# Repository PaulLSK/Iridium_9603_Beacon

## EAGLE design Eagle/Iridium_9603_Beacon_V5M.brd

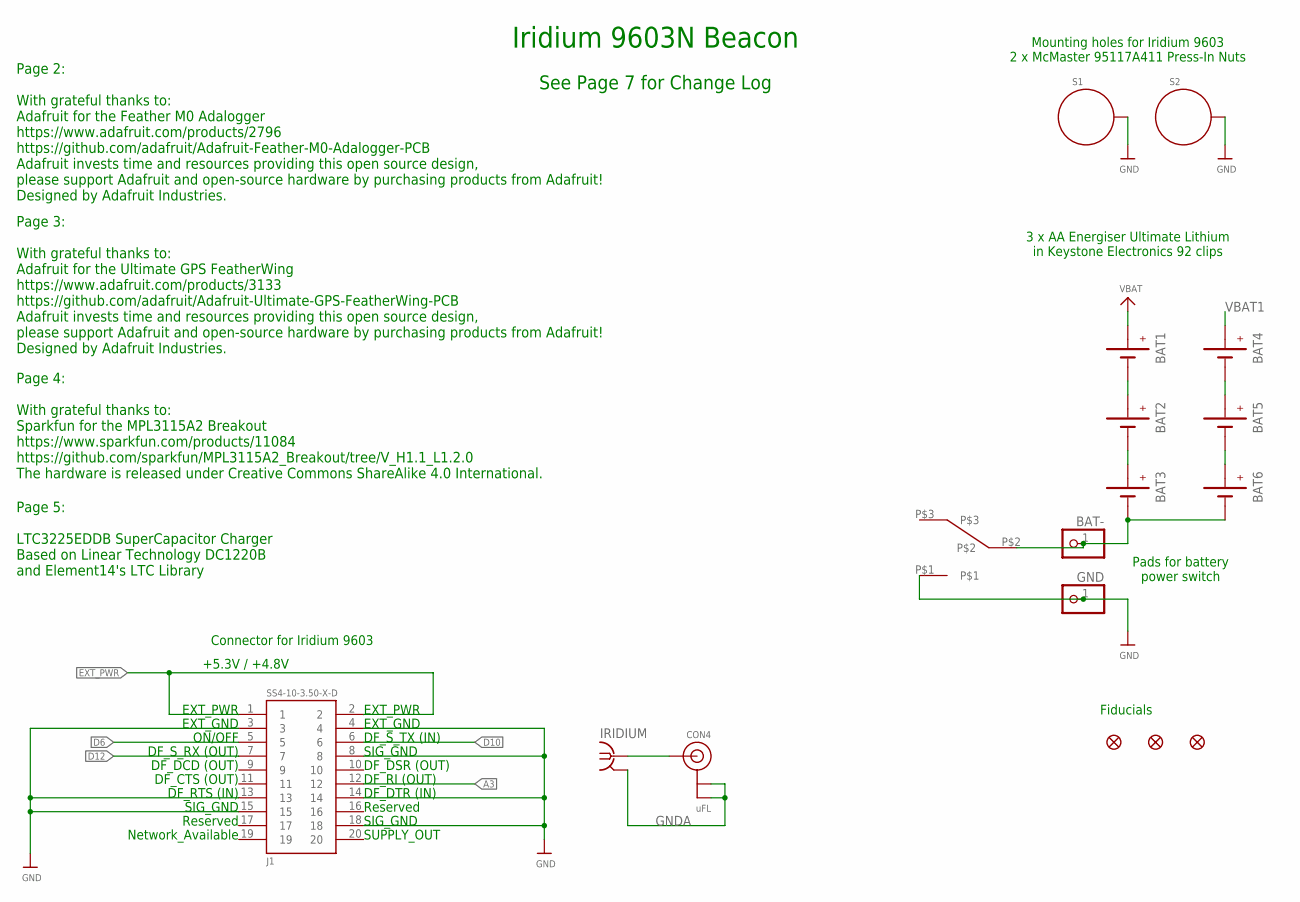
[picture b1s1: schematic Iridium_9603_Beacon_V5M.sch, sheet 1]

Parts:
BAT1, BAT2, BAT3, BAT4, BAT5, BAT6: BATTERYKEYSTONE92; BATTERY-AAA-KEYSTONE92
BAT-: PINHD-1X1; 1X01
CON4: uFL; U.FL
FD1, FD2, FD3: FIDUCIAL1X2; FIDUCIAL-1X2
GND: PINHD-1X1; 1X01
IRIDIUM: SMA-142-0711-821/826; J502-ND-142-0711-821/826
J1: SS4-10-3.50-X-D
S1, S2: STANDOFF_ELECTRICALMCMASTER-95117A411; STANDOFF-ELECTRICAL-MCMASTER-95117A411
U53: 7101K2AV2QE; AV2_SPDT

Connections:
A3: J1.12; also elsewhere on the board
D6: J1.5; also elsewhere on the board
D10: J1.6; also elsewhere on the board
D12: J1.7; also elsewhere on the board
EXT_PWR: J1.1, J1.2; also elsewhere on the board
GND: GND.1, J1.3, J1.4, J1.8, J1.13, J1.14, J1.15, J1.18, S1.P1, S2.P1, U53.P$1; also elsewhere on the board
GNDA: CON4.1 (GND), CON4.2 (GND), IRIDIUM.G@1 (2), IRIDIUM.G@2 (2), IRIDIUM.G@3 (2), IRIDIUM.G@4 (2)
unnamed: CON4.3 (SIGNAL), IRIDIUM.1
unnamed: BAT1.GND@1 (-), BAT1.GND@2 (-), BAT2.PWR@1 (+), BAT2.PWR@2 (+)
unnamed: BAT3.GND@1 (-), BAT3.GND@2 (-), BAT6.GND@1 (-), BAT6.GND@2 (-), BAT-.1, U53.P$2
unnamed: BAT2.GND@1 (-), BAT2.GND@2 (-), BAT3.PWR@1 (+), BAT3.PWR@2 (+)
unnamed: BAT4.GND@1 (-), BAT4.GND@2 (-), BAT5.PWR@1 (+), BAT5.PWR@2 (+)
unnamed: BAT5.GND@1 (-), BAT5.GND@2 (-), BAT6.PWR@1 (+), BAT6.PWR@2 (+)
VBAT: BAT1.PWR@1 (+), BAT1.PWR@2 (+); also elsewhere on the board
VBAT1: BAT4.PWR@1 (+), BAT4.PWR@2 (+); also elsewhere on the board

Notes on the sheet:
3 x AA Energiser Ultimate Lithium in Keystone Electronics 92 clips
Connector for Iridium 9603
Mounting holes for Iridium 9603 2 x McMaster 95117A411 Press-In Nuts
Iridium 9603N Beacon
Page 2: With grateful thanks to: Adafruit for the Feather M0 Adalogger https://www.adafruit.com/products/2796 https://github.com/adafruit/Adafruit-Feather-M0-Adalogger-PCB Adafruit invests time and resources providing this open source design, please support Adafruit and open-source hardware by purc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
Page 3: With grateful thanks to: Adafruit for the Ultimate GPS FeatherWing https://www.adafruit.com/products/3133 https://github.com/adafruit/Adafruit-Ultimate-GPS-FeatherWing-PCB Adafruit invests time and resources providing this open source design, please support Adafruit and open-source hardware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
Page 4: With grateful thanks to: Sparkfun for the MPL3115A2 Breakout https://www.sparkfun.com/products/11084 https://github.com/sparkfun/MPL3115A2_Breakout/tree/V_H1.1_L1.2.0 The hardware is released under Creative Commons ShareAlike 4.0 International.
EXT_PWR
EXT_GND
ON/OFF
DF_S_RX (OUT)
DF_DCD (OUT)
DF_CTS (OUT)
DF_RTS (IN)
SIG_GND
Reserved
Network_Available
DF_S_TX (IN)
DF_DSR (OUT)
DF_RI (OUT)
DF_DTR (IN)
SUPPLY_OUT
Page 5: LTC3225EDDB SuperCapacitor Charger Based on Linear Technology DC1220B and Element14's LTC Library
+5.3V / +4.8V
Fiducials
See Page 7 for Change Log
Pads for battery power switch

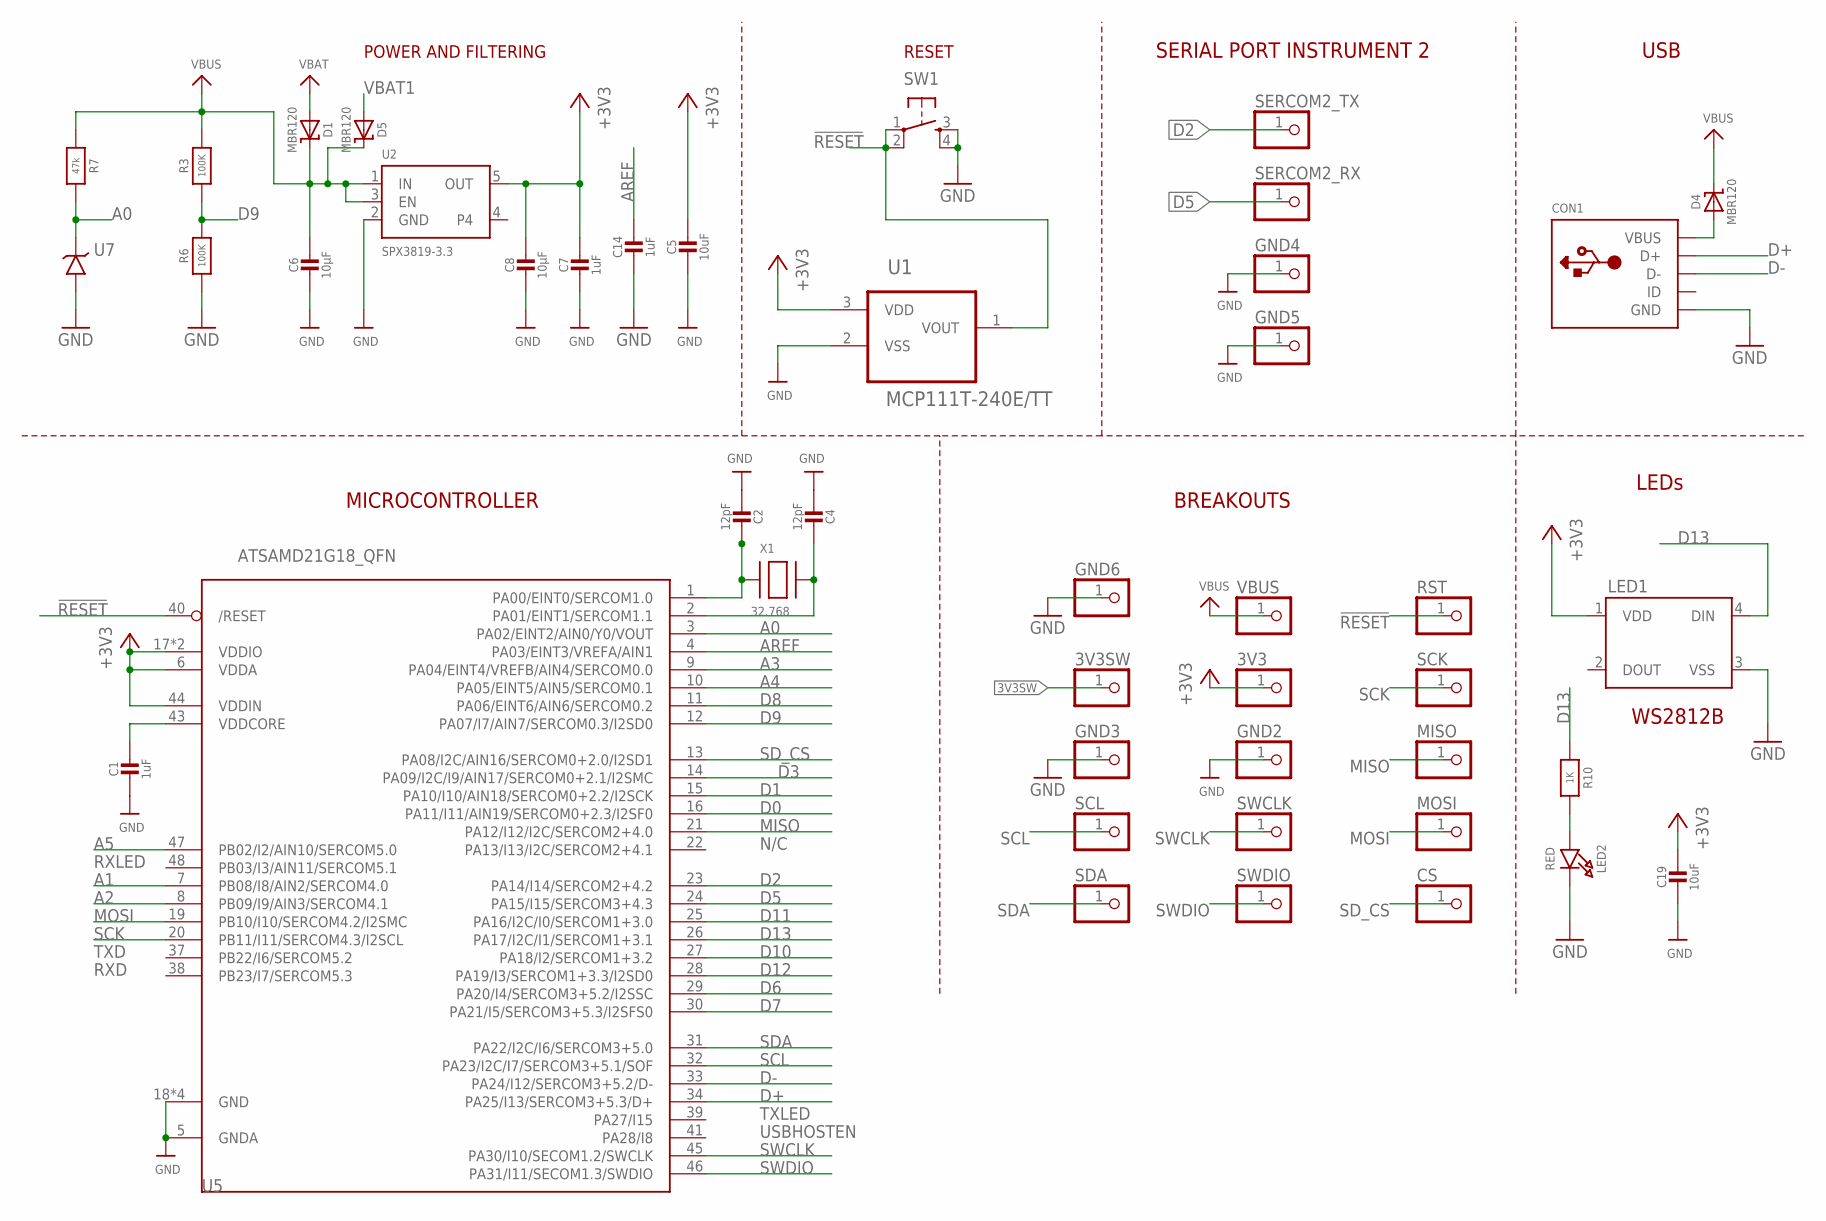
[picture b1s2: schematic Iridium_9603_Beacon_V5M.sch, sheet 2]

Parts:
3V3, 3V3SW: PINHD-1X1; 1X01
C1, C7, C14: 1uF; 0603-NO
C2, C4: 12pF; 0603-NO
C5, C19: 10uF; 0805-NO
C6, C8: 10µF; 0805-NO
CON1: USBFCI_10103594; FCI_10103594
CS: PINHD-1X1; 1X01
D1, D4, D5: MBR120; SOD-123
GND2, GND3, GND4, GND5, GND6: PINHD-1X1; 1X01
LED1: WS2812B
LED2: RED; CHIPLED_0805_NOOUTLINE
MISO: PINHD-1X1; 1X01
MOSI: PINHD-1X1; 1X01
R3, R6: 100K; 0805-NO
R7: 47k; 0603-NO
R10: 1K; 0603-NO
RST: PINHD-1X1; 1X01
SCK: PINHD-1X1; 1X01
SCL: PINHD-1X1; 1X01
SDA: PINHD-1X1; 1X01
SERCOM2_RX, SERCOM2_TX: PINHD-1X1; 1X01
SW1: SWITCH_SPST_4_PINRECT; TACTILE_SWITCH_SMD_4.6X2.8MM
SWCLK: PINHD-1X1; 1X01
SWDIO: PINHD-1X1; 1X01
U1: MCP111T-240E/TT; SOT95P237X112-3N; MPN MCP111T-240E/TT
U2: SPX3819-3.3; SOT23-5
U5: ATSAMD21G18_QFN; TQFN48_7MM
U7: LT1634-1,25BMCMS8; MSOP8
VBUS: PINHD-1X1; 1X01
X1: 32.768; XTAL3215

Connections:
3V3SW: 3V3SW.1; also elsewhere on the board
!RESET: RST.1, SW1.1, SW1.2, U1.1 (VOUT), U5.40 (/RESET)
+3V3: 3V3.1, C5.1, C7.1, C8.1, C19.1, LED1.1 (VDD), U1.3 (VDD), U2.5 (OUT), U5.6 (VDDA), U5.17 (VDDIO), U5.36 (VDDIO), U5.44 (VDDIN); also elsewhere on the board
A0: R7.2, U5.3 (PA02/EINT2/AIN0/Y0/VOUT), U7.6 (VOUT)
A1: U5.7 (PB08/I8/AIN2/SERCOM4.0); also elsewhere on the board
A2: U5.8 (PB09/I9/AIN3/SERCOM4.1)
A3: U5.9 (PA04/EINT4/VREFB/AIN4/SERCOM0.0); also elsewhere on the board
A4: U5.10 (PA05/EINT5/AIN5/SERCOM0.1)
A5: U5.47 (PB02/I2/AIN10/SERCOM5.0); also elsewhere on the board
AREF: C14.1, U5.4 (PA03/EINT3/VREFA/AIN1)
D0: U5.16 (PA11/I11/AIN19/SERCOM0+2.3/I2SF0); also elsewhere on the board
D1: U5.15 (PA10/I10/AIN18/SERCOM0+2.2/I2SCK); also elsewhere on the board
D2: SERCOM2_TX.1, U5.23 (PA14/I14/SERCOM2+4.2)
D3: U5.14 (PA09/I2C/I9/AIN17/SERCOM0+2.1/I2SMC); also elsewhere on the board
D5: SERCOM2_RX.1, U5.24 (PA15/I15/SERCOM3+4.3)
D6: U5.29 (PA20/I4/SERCOM3+5.2/I2SSC); also elsewhere on the board
D7: U5.30 (PA21/I5/SERCOM3+5.3/I2SFS0); also elsewhere on the board
D8: U5.11 (PA06/EINT6/AIN6/SERCOM0.2); also elsewhere on the board
D9: R3.1, R6.2, U5.12 (PA07/I7/AIN7/SERCOM0.3/I2SD0)
D10: U5.27 (PA18/I2/SERCOM1+3.2); also elsewhere on the board
D11: U5.25 (PA16/I2C/I0/SERCOM1+3.0); also elsewhere on the board
D12: U5.28 (PA19/I3/SERCOM1+3.3/I2SD0); also elsewhere on the board
D13: LED1.4 (DIN), R10.1, U5.26 (PA17/I2C/I1/SERCOM1+3.1)
D+: CON1.D+, U5.34 (PA25/I13/SERCOM3+5.3/D+)
D-: CON1.D-, U5.33 (PA24/I12/SERCOM3+5.2/D-)
GND: C1.2, C2.2, C4.2, C5.2, C6.2, C7.2, C8.2, C14.2, C19.2, CON1.BASE@1 (GND), CON1.BASE@2 (GND), CON1.GND, CON1.SPRT@1 (GND), CON1.SPRT@2 (GND), CON1.SPRT@3 (GND), CON1.SPRT@4 (GND), GND2.1, GND3.1, GND4.1, GND5.1, GND6.1, LED1.3 (VSS), LED2.C, R6.1, SW1.3, SW1.4, U1.2 (VSS), U2.2 (GND), U5.5 (GNDA), U5.18 (GND), U5.35 (GND), U5.42 (GND), U5.THERMAL (GND), U7.4 (GND); also elsewhere on the board
MISO: MISO.1, U5.21 (PA12/I12/I2C/SERCOM2+4.0)
MOSI: MOSI.1, U5.19 (PB10/I10/SERCOM4.2/I2SMC)
unnamed: LED2.A, R10.2
unnamed: C2.1, U5.1 (PA00/EINT0/SERCOM1.0), X1.P$1
unnamed: C4.1, U5.2 (PA01/EINT1/SERCOM1.1), X1.P$2
unnamed: CON1.VBUS, D4.A
SCK: SCK.1, U5.20 (PB11/I11/SERCOM4.3/I2SCL)
SCL: SCL.1, U5.32 (PA23/I2C/I7/SERCOM3+5.1/SOF); also elsewhere on the board
SDA: SDA.1, U5.31 (PA22/I2C/I6/SERCOM3+5.0); also elsewhere on the board
SD_CS: CS.1, U5.13 (PA08/I2C/AIN16/SERCOM0+2.0/I2SD1)
SWCLK: SWCLK.1, U5.45 (PA30/I10/SECOM1.2/SWCLK)
SWDIO: SWDIO.1, U5.46 (PA31/I11/SECOM1.3/SWDIO)
VBAT: D1.A; also elsewhere on the board
VBAT1: D5.A; also elsewhere on the board
VBUS: C6.1, D1.C, D4.C, D5.C, R3.2, R7.1, U2.1 (IN), U2.3 (EN), VBUS.1; also elsewhere on the board
VDDCORE1: C1.1, U5.43 (VDDCORE)

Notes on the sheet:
POWER AND FILTERING
RESET
N/C
TXLED
USBHOSTEN
RXLED
TXD
RXD
USB
BREAKOUTS
LEDs
MICROCONTROLLER
WS2812B
SERIAL PORT INSTRUMENT 2

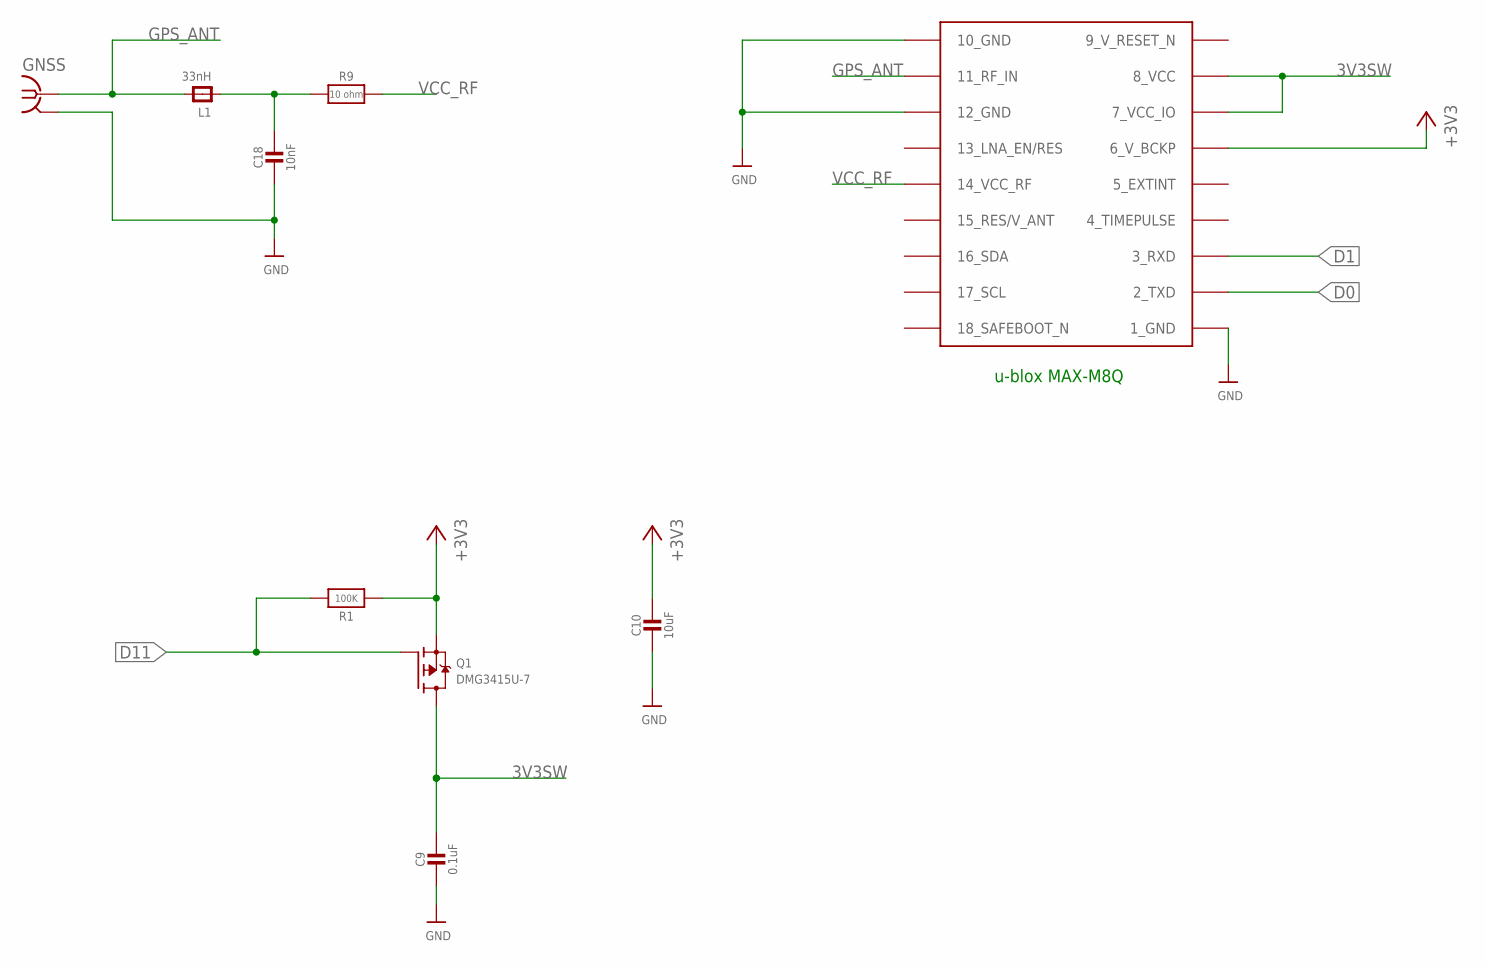
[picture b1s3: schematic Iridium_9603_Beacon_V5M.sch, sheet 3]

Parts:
C9: 0.1uF; 0805-NO
C10: 10uF; 0805-NO
C18: 10nF; 0805-NO
GNSS: SMA-142-0711-821/826; J502-ND-142-0711-821/826
L1: 33nH; 0805-NO
Q1: DMG3415U-7; SOT23-WIDE
R1: 100K; 0805-NO
R9: 10 ohm; 0805-NO
U6: MAX-M8

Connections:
3V3SW: C9.1, Q1.3 (D), U6.7_VCC_IO, U6.8_VCC; also elsewhere on the board
9_V_RESET_N: U6.9_RESET_N (9_V_RESET_N)
+3V3: C10.1, Q1.2 (S), R1.1, U6.6_V_BCKP; also elsewhere on the board
D0: U6.2_TXD; also elsewhere on the board
D1: U6.3_RXD; also elsewhere on the board
D11: Q1.1 (G), R1.2; also elsewhere on the board
GND: C9.2, C10.2, C18.2, GNSS.G@1 (2), GNSS.G@2 (2), GNSS.G@3 (2), GNSS.G@4 (2), U6.1_GND, U6.10_GND, U6.12_GND; also elsewhere on the board
GPS_ANT: GNSS.1, L1.2, U6.11_RF_IN
unnamed: C18.1, L1.1, R9.1
VCC_RF: R9.2, U6.14_VCC_RF

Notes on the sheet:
u-blox MAX-M8Q

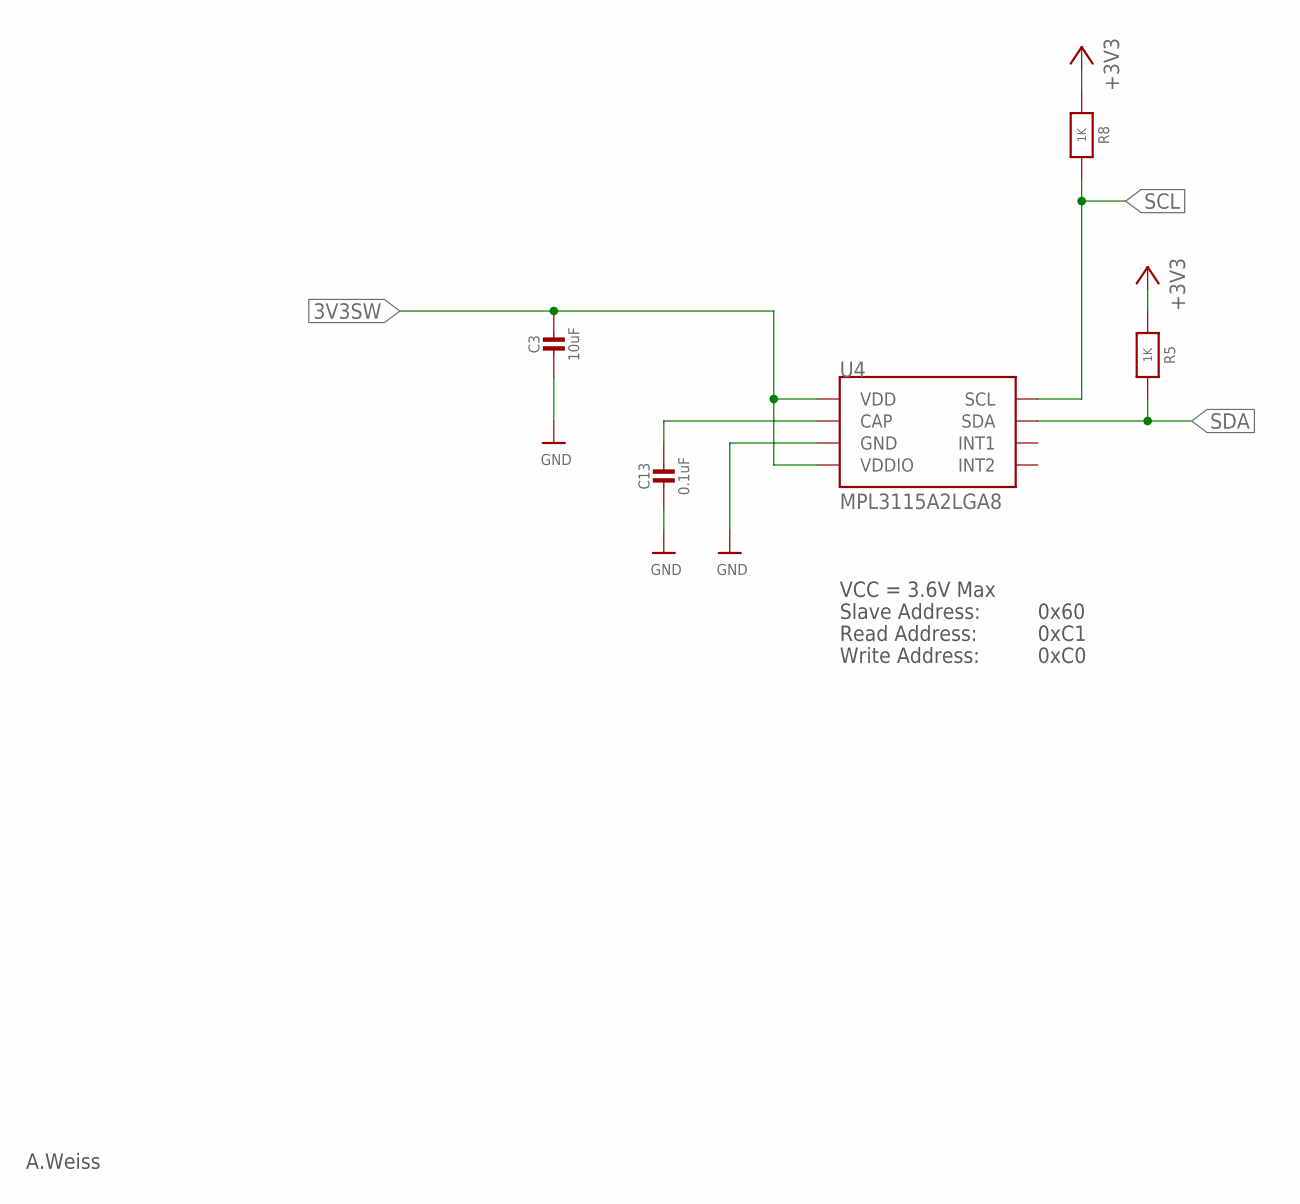
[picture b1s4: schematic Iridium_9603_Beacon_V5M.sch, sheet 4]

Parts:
C3: 10uF; 0805-NO
C13: 0.1uF; 0805-NO
R5, R8: 1K; 0603-NO
U4: MPL3115A2LGA8; LGA8

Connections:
3V3SW: C3.1, U4.1 (VDD), U4.4 (VDDIO); also elsewhere on the board
+3V3: R5.1, R8.1; also elsewhere on the board
GND: C3.2, C13.2, U4.3 (GND); also elsewhere on the board
unnamed: C13.1, U4.2 (CAP)
SCL: R8.2, U4.8 (SCL); also elsewhere on the board
SDA: R5.2, U4.7 (SDA); also elsewhere on the board

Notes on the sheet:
A.Weiss
VCC = 3.6V Max
Read Address:
Write Address:
Slave Address:
0x60
0xC1
0xC0

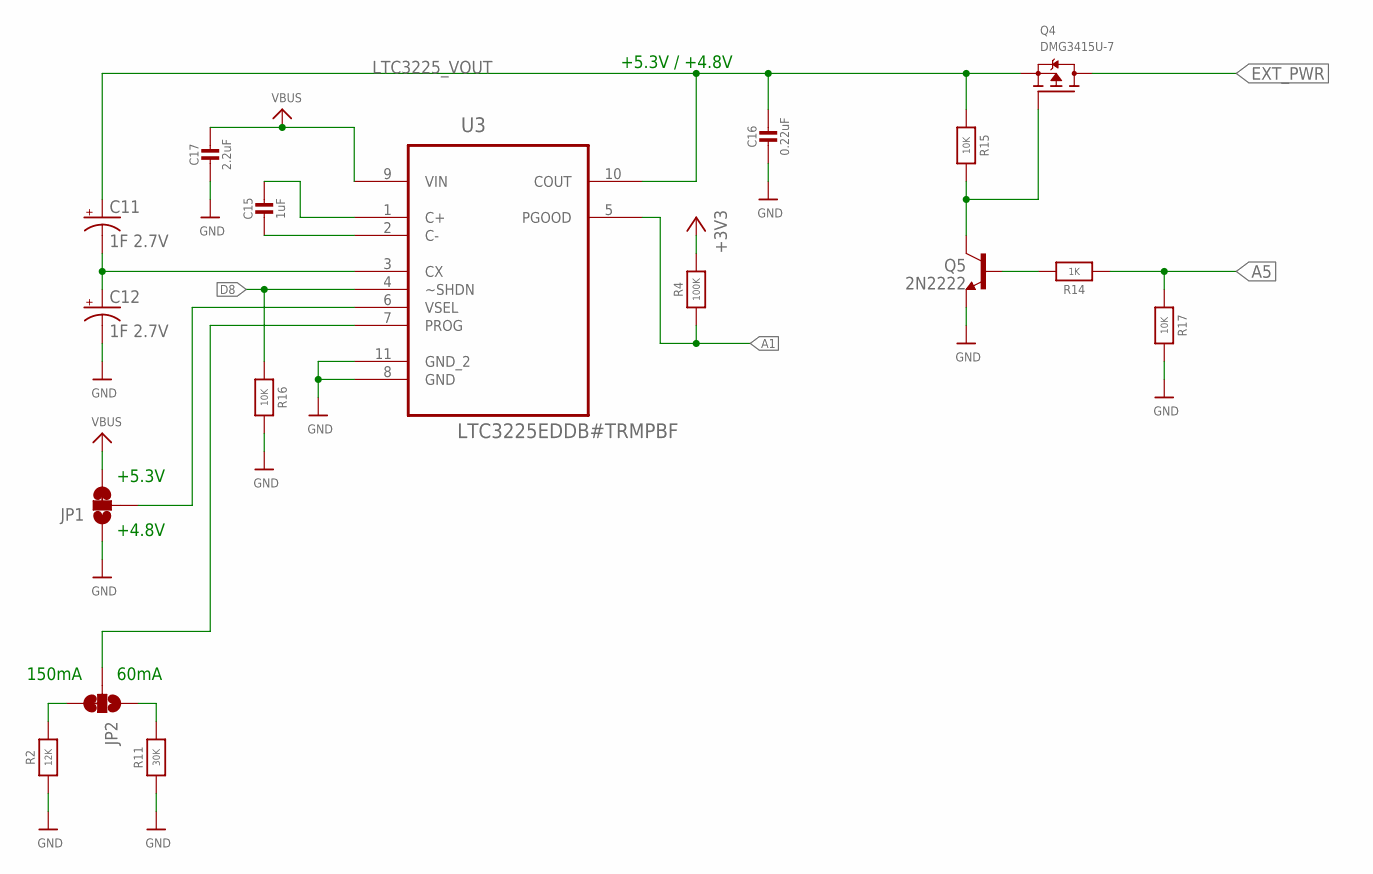
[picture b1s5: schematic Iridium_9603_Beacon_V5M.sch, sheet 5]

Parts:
C11, C12: 1F 2.7V; CPOL-RADIAL-1F-2.7V
C15: 1uF; 0603-NO
C16: 0.22uF; 0603-NO
C17: 2.2uF; 0805-NO
JP1, JP2: JUMPER-PAD-3-2OF3_NC_BY_TRACE_LARGE; PAD-JUMPER-3-2OF3_NC_BY_TRACE_YES_SILK_LARGE
Q4: DMG3415U-7; SOT23-WIDE
Q5: 2N2222; SOT23-BEC
R2: 12K; 0805-NO
R4: 100K; 0805-NO
R11: 30K; 0805-NO
R14: 1K; 0603-NO
R15, R16, R17: 10K; 0603-NO
U3: LTC3225EDDB#TRMPBF; DFN300X200-10L

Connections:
+3V3: R4.2; also elsewhere on the board
A1: R4.1, U3.5 (PGOOD); also elsewhere on the board
A5: R14.1, R17.1; also elsewhere on the board
D8: R16.1, U3.4 (~SHDN); also elsewhere on the board
EXT_PWR: Q4.3 (D); also elsewhere on the board
GND: C12.-, C16.2, C17.2, JP1.1, Q5.E, R2.1, R11.1, R16.2, R17.2, U3.8 (GND), U3.11 (GND_2); also elsewhere on the board
LTC3225_VOUT: C11.+, C16.1, Q4.2 (S), R15.1, U3.10 (COUT)
unnamed: C11.-, C12.+, U3.3 (CX)
unnamed: C15.2, U3.2 (C-)
unnamed: C15.1, U3.1 (C+)
unnamed: JP2.2, U3.7 (PROG)
unnamed: JP1.2, U3.6 (VSEL)
unnamed: JP2.3, R2.2
unnamed: JP2.1, R11.2
unnamed: Q4.1 (G), Q5.C, R15.2
unnamed: Q5.B, R14.2
VBUS: C17.1, JP1.3, U3.9 (VIN); also elsewhere on the board

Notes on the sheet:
+5.3V / +4.8V
+5.3V
+4.8V
150mA
60mA

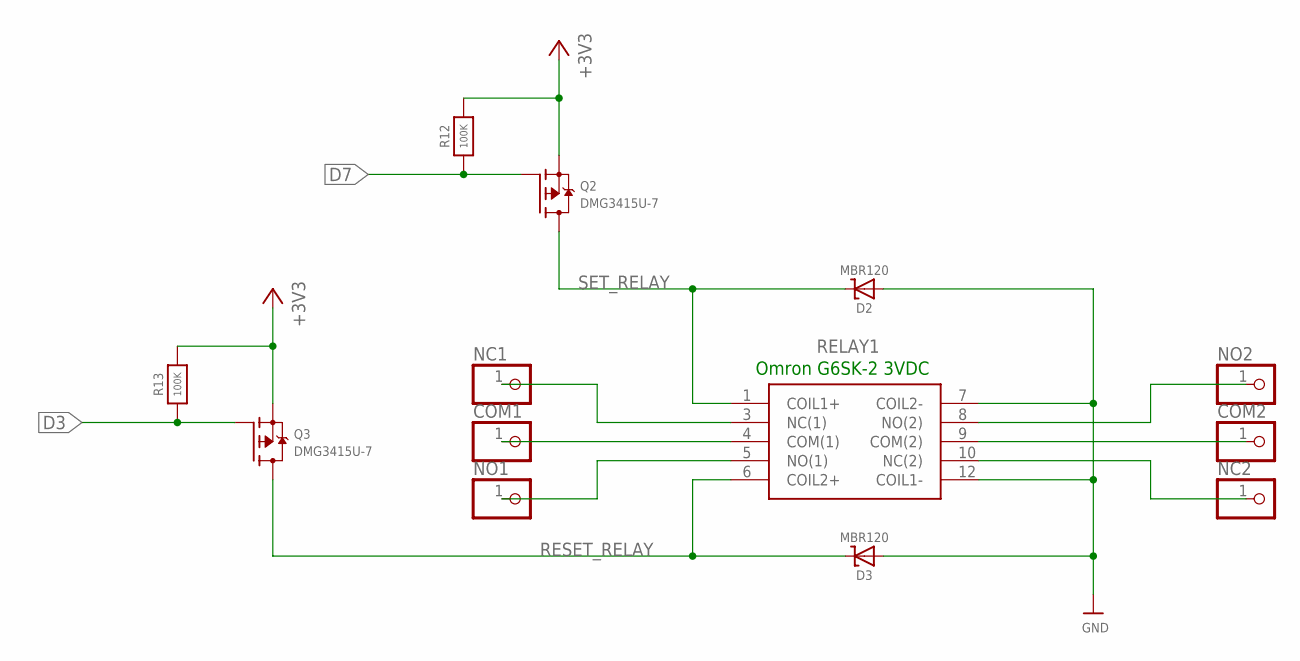
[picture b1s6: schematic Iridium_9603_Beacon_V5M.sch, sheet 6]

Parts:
COM1, COM2: PINHD-1X1; 1X01
D2, D3: MBR120; SOD-123
NC1, NC2: PINHD-1X1; 1X01
NO1, NO2: PINHD-1X1; 1X01
Q2, Q3: DMG3415U-7; SOT23-WIDE
R12, R13: 100K; 0805-NO
RELAY1: G6SK-2_DC5; G6SK2DC5

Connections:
+3V3: Q2.2 (S), Q3.2 (S), R12.2, R13.2; also elsewhere on the board
D3: Q3.1 (G), R13.1; also elsewhere on the board
D7: Q2.1 (G), R12.1; also elsewhere on the board
GND: D2.A, D3.A, RELAY1.7 (COIL2-), RELAY1.12 (COIL1-); also elsewhere on the board
unnamed: NC1.1, RELAY1.3 (NC(1))
unnamed: COM1.1, RELAY1.4 (COM(1))
unnamed: NO1.1, RELAY1.5 (NO(1))
unnamed: NO2.1, RELAY1.8 (NO(2))
unnamed: COM2.1, RELAY1.9 (COM(2))
unnamed: NC2.1, RELAY1.10 (NC(2))
RESET_RELAY: D3.C, Q3.3 (D), RELAY1.6 (COIL2+)
SET_RELAY: D2.C, Q2.3 (D), RELAY1.1 (COIL1+)

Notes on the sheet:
Omron G6SK-2 3VDC

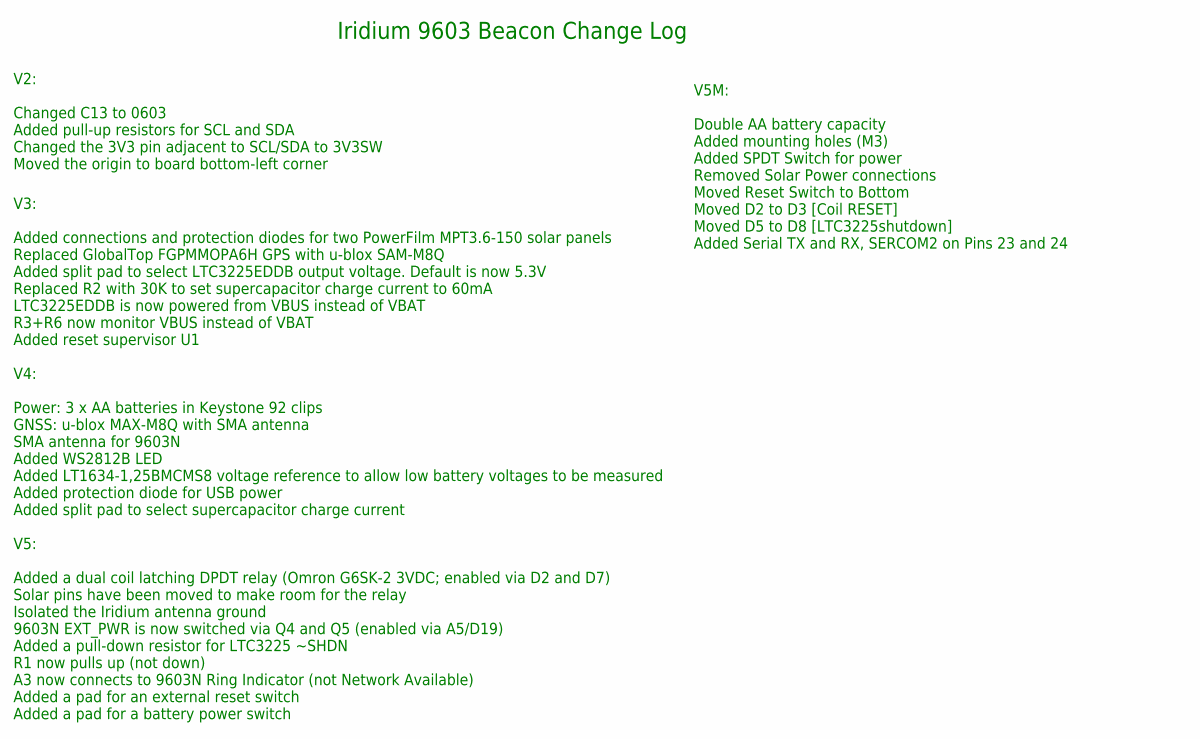
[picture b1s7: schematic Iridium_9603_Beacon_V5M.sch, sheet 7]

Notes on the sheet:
V2: Changed C13 to 0603 Added pull-up resistors for SCL and SDA Changed the 3V3 pin adjacent to SCL/SDA to 3V3SW Moved the origin to board bottom-left corner
Iridium 9603 Beacon Change Log
V3: Added connections and protection diodes for two PowerFilm MPT3.6-150 solar panels Replaced GlobalTop FGPMMOPA6H GPS with u-blox SAM-M8Q Added split pad to select LTC3225EDDB output voltage. Default is now 5.3V Replaced R2 with 30K to set supercapacitor charge current to 60mA LTC3225EDDB is now 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
V4: Power: 3 x AA batteries in Keystone 92 clips GNSS: u-blox MAX-M8Q with SMA antenna SMA antenna for 9603N Added WS2812B LED Added LT1634-1,25BMCMS8 voltage reference to allow low battery voltages to be measured Added protection diode for USB power Added split pad to select supercapacitor charge 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
V5: Added a dual coil latching DPDT relay (Omron G6SK-2 3VDC; enabled via D2 and D7) Solar pins have been moved to make room for the relay Isolated the Iridium antenna ground 9603N EXT_PWR is now switched via Q4 and Q5 (enabled via A5/D19) Added a pull-down resistor for LTC3225 ~SHDN R1 now pulls u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
V5M: Double AA battery capacity Added mounting holes (M3) Added SPDT Switch for power Removed Solar Power connections Moved Reset Switch to Bottom Moved D2 to D3 [Coil RESET] Moved D5 to D8 [LTC3225shutdown] Added Serial TX and RX, SERCOM2 on Pins 23 and 24

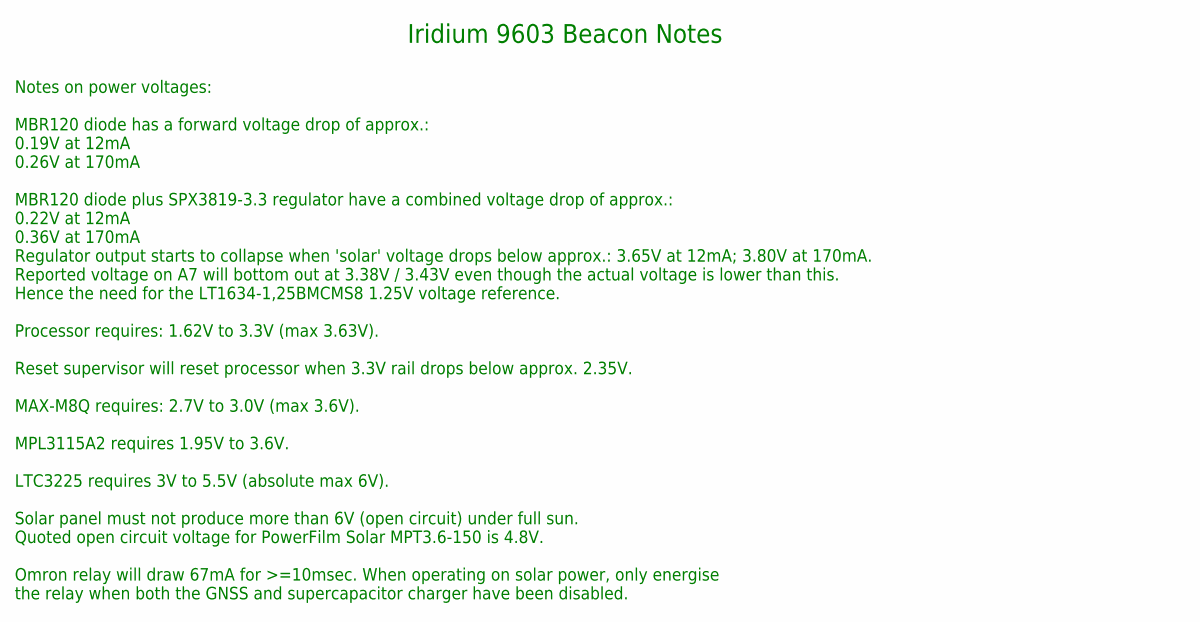
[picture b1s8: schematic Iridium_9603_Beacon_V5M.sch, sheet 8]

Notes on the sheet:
Iridium 9603 Beacon Notes
Notes on power voltages: MBR120 diode has a forward voltage drop of approx.: 0.19V at 12mA 0.26V at 170mA MBR120 diode plus SPX3819-3.3 regulator have a combined voltage drop of approx.: 0.22V at 12mA 0.36V at 170mA Regulator output starts to collapse when 'solar' voltage drops below approx.: 3.65V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

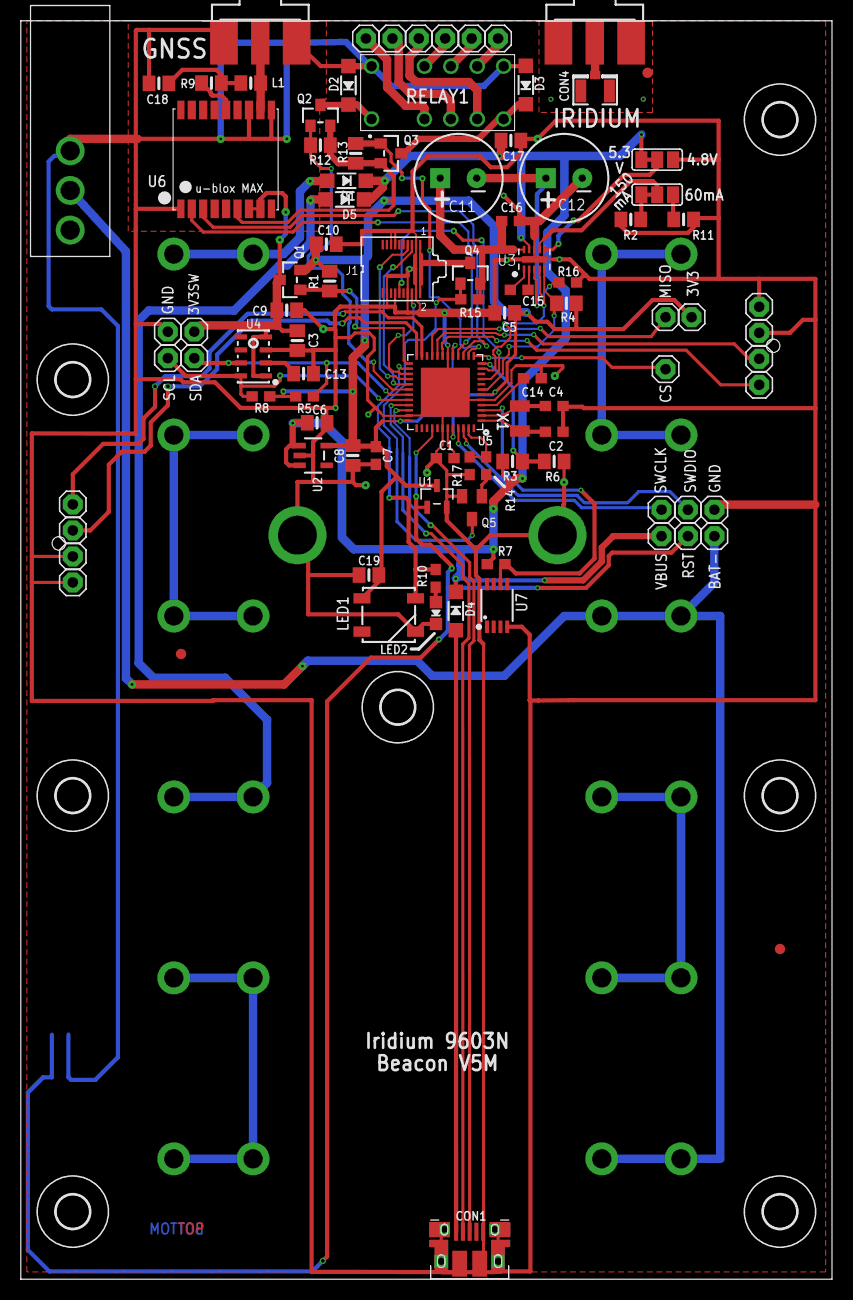
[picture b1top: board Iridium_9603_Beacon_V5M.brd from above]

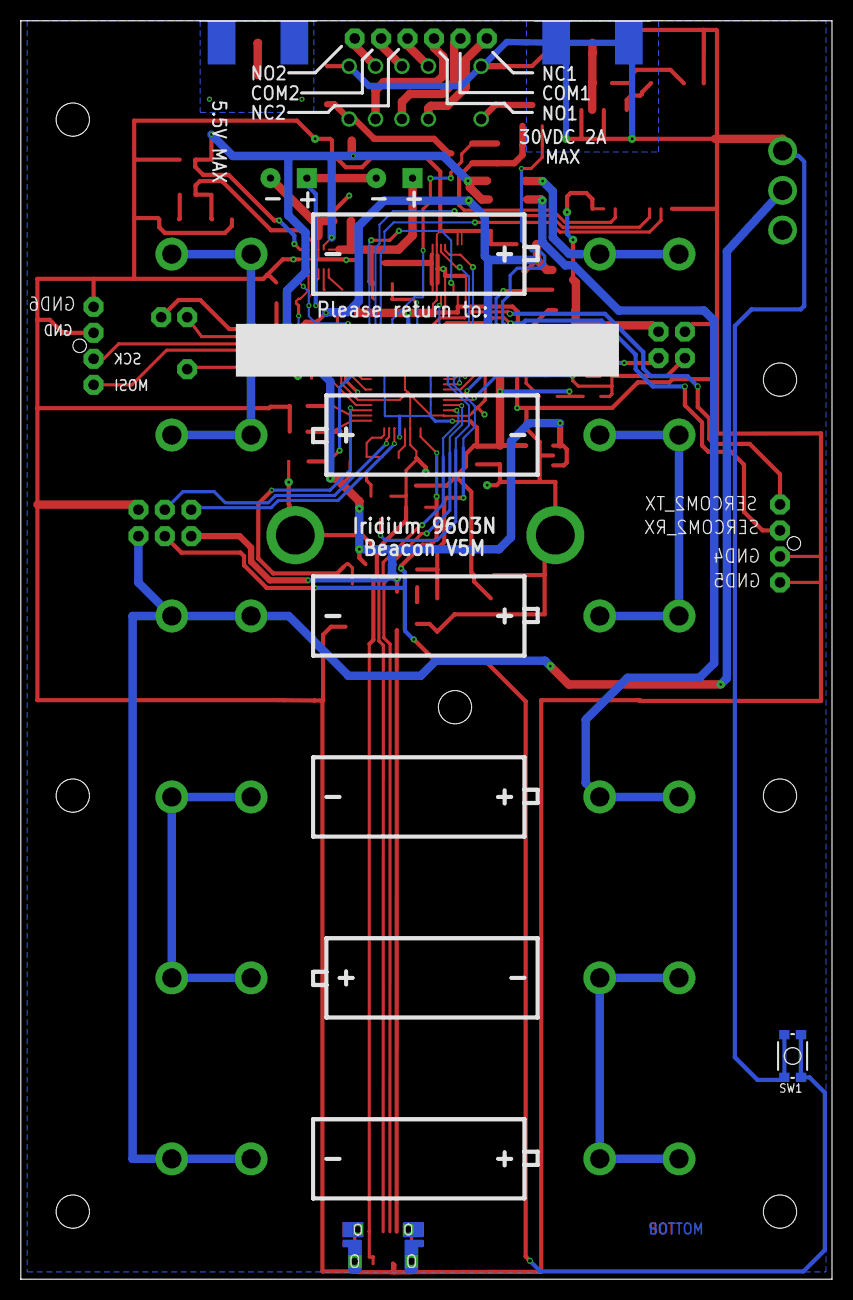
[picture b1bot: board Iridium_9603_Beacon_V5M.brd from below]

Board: 2 copper layers, 78.0 x 121.0 mm, 112 parts (7 on the bottom side), 70 nets.

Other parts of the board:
U$2, U$40, U$48, U$49, U$50, U$51, U$52: 3,2

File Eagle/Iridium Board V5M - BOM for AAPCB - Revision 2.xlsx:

Mfg Part # | Description | Value | Pkg | Description Value Pkg *AAPCB Format* | Ref. Des. | Qty | DNI | Notes | Mfg (Optional) | Vendor (Optional) | Vendor Part # (Optional) | Alternate Mfg Part # (Optional) | Type (Optional)
CL10B105KP8NNNC | CAP CER | 1uF 10V 10% | 0603 SMD | CAP CER 1uF 10V 10% 0603 SMD | C1,C7,C14,C15 | 4 |  |  | Samsung | Digi-key | 1276-1946-1-ND
500R14N120JV4T | CAP CER | 12 pF 50V 5% | 0603 SMD | CAP CER 12 pF 50V 5% 0603 SMD | C2,C4 | 2 |  |  | Johanson | Digi-key | 709-1141-1-ND
CL21X106KPCLRNC | CAP CER | 10uF 10V 10% | 0805 SMD | CAP CER 10uF 10V 10% 0805 SMD | C3,C5,C6,C8,C10,C19 | 6 |  |  | Samsung | Digi-key | 1276-2717-1-ND
08053C104KAT2A | CAP CER | 0.1UF 25V 10% | 0805 SMD | CAP CER 0.1UF 25V 10% 0805 SMD | C9,C13 | 2 |  |  | AVX | Digi-key | 478-3755-1-ND
CC0603KRX7R7BB224 | CAP CER | 0.22uF 16V 10% | 0603 SMD | CAP CER 0.22uF 16V 10% 0603 SMD | C16 | 1 |  | Alternate Part: 220nF 25V ±10% 0603 Samsung | Yageo | Digi-key | 311-1426-1-ND
CL21B225KAFNFNE | CAP CER | 2.2uF 25V 10% | 0805 SMD | CAP CER 2.2uF 25V 10% 0805 SMD | C17 | 1 |  |  | Samsung | Digi-key | 1276-2953-1-ND
CL21B103KBANNNC | CAP CER | 10nF 50V 10% | 0805 SMD | CAP CER 10nF 50V 10% 0805 SMD | C18 | 1 |  |  | Samsung | Digi-key | 1276-1015-6-ND
10103594-0001LF | CONN RCPT | USB2.0 | MICRO B SMD | CONN RCPT USB2.0 MICRO B SMD | CON1 | 1 |  |  | Amphenol | Digi-key | 609-4050-1-ND
U.FL-R-SMT(01) | CONN U.FL RCPT | STR 50 OHM | SMD | CONN U.FL RCPT STR 50 OHM SMD | CON4 | 1 |  |  | Hirose | Digi-key | H9161-ND
MBR120VLSFT1G | DIODE SCHOTTKY | 20V 1A | SOD-123 SMD | DIODE SCHOTTKY 20V 1A SOD-123 SMD | D1,D2,D3,D4 | 4 |  |  | ON Semi | Digi-key | MBR120VLSFT1GOSDKR-ND
SS4-10-3.50-L-D-K-TR | .4MM SOCKET STRIP | 20 POS | SMD | .4MM SOCKET STRIP 20 POS SMD | J1 | 1 |  |  | Samtec | Digi-key | SAM13255CT-ND
74476013C | FIXED IND | 33nH 500mA 270 MOHM | 0805 SMD | FIXED IND 33nH 500mA 270 MOHM 0805 SMD | L1 | 1 |  |  | Wurth Elec | Digi-key | 732-1783-1-ND
COM-11821 | LED DISCRETE | SERIAL RGB | SMD | LED DISCRETE SERIAL RGB SMD | LED1 | 1 |  |  | Sparkfun | Digi-key | 1568-1800-ND
150080RS75000 | LED | RED CLEAR | 0805 SMD | LED RED CLEAR 0805 SMD | LED2 | 1 |  |  | Wurth Elec | Digi-key | 732-4984-6-ND
DMP2045U-7 | MOSFET P-CHAN | 24V | SOT-23 SMD | MOSFET P-CHAN 24V SOT-23 SMD | Q1,Q2,Q3,Q4 | 4 |  |  | Diodes Inc | Digi-key | DMP2045U-7DIDKR-ND
MMBT2222A-TP | TRANS NPN | 40V 0.6A | SOT-23 SMD | TRANS NPN 40V 0.6A SOT-23 SMD | Q5 | 1 |  |  | Micro Commercial | Digi-key | MMBT2222ATPMSDKR-ND
RMCF0805FG100K | RES | 100K 1% 1/8W | 0805 SMD | RES 100K 1% 1/8W 0805 SMD | R1,R3,R4,R6,R12,R13 | 6 |  |  | Stackpole Elec | Digi-key | RMCF0805FG100KCT-ND
RMCF0805FT12K0 | RES | 12K 1% 1/8W | 0805 SMD | RES 12K 1% 1/8W 0805 SMD | R2 | 1 |  |  | Stackpole Elec | Digi-key | RMCF0805FT12K0DKR-ND
RC1608F102CS | RES | 1K 1% 1/10W | 0603 SMD | RES 1K 1% 1/10W 0603 SMD | R5,R8,R10,R14 | 3 |  |  | Samsung | Digi-key | 1276-3484-6-ND
RC1608F473CS | RES | 47K 1% 1/10W | 0603 SMD | RES 47K 1% 1/10W 0603 SMD | R7 | 1 |  |  | Samsung | Digi-key | 1276-4808-6-ND
CRG0805F10R | RES | 10 1% 1/8W | 0805 SMD | RES 10 1% 1/8W 0805 SMD | R9 | 1 |  |  | TE Connectivity | Digi-key | A106055DKR-ND
CRG0805F30K | RES | 30K 1% 1/8W | 0805 SMD | RES 30K 1% 1/8W 0805 SMD | R11 | 1 |  |  | TE Connectivity | Digi-key | A126360DKR-ND
RNCP0603FTD10K0 | RES | 10K 1% 1/8W | 0603 SMD | RES 10K 1% 1/8W 0603 SMD | R15,R16,R17 | 3 |  |  | Stackpole Elec | Digi-key | RNCP0603FTD10K0CT-ND
KMR231NG LFS | SWITCH TACTILE SPST-NO | 0.05A 32V | SMD | SWITCH TACTILE SPST-NO 0.05A 32V SMD | SW1 | 1 |  |  | C&K | Digi-key | CKN10246CT-ND
MCP111T-240E/TT | IC VOLT DET | 2.32V LOW | SOT-23-3 SMD | IC VOLT DET 2.32V LOW SOT-23-3 SMD | U1 | 1 |  |  | Microchip | Digi-key | MCP111T-240E/TTDKR-ND
SPX3819M5-L-3-3/TR | IC REG LINEAR | 3.3V 500mA | SOT-23-5 SMD | IC REG LINEAR 3.3V 500mA SOT-23-5 SMD | U2 | 1 |  |  | MaxLinear | Digi-key | 1016-1873-6-ND
LTC3225EDDB-1#TRMPBF | IC SUPERCAP CHARGER | 150mA | 10-DFN SMD | IC SUPERCAP CHARGER 150mA 10-DFN SMD | U3 | 1 |  |  | Linear | Digi-key | LTC3225EDDB-1#TRMPBFCT-ND
MPL3115A2 | IC ALTIMETER I2C |  | 8-LGA SMD | IC ALTIMETER I2C 8-LGA SMD | U4 | 1 |  |  | NXP USA | Digi-key | MPL3115A2-ND
ATSAMD21G18A-MFT | IC MCU 32BIT 256KB FLASH |  | 48-QFN | IC MCU 32BIT 256KB FLASH 48-QFN | U5 | 1 |  |  | Microchip | Digi-key | ATSAMD21G18A-MFTDKR-ND
MAX-M8Q-0 | IC RECEIVER GPS/GNSS |  | 18LCC SMD | IC RECEIVER GPS/GNSS 18LCC SMD | U6 | 1 |  |  | U-Blox America | Digi-key | 672-1003-6-ND
LT1634BCMS8-1.25#PBF | IC VREF SHUNT | 1.25V | 8-MSOP SMD | IC VREF SHUNT 1.25V 8-MSOP SMD | U7 | 1 |  |  | Linear | Digi-key | LT1634BCMS8-1.25#PBF-ND
FC-135 32.7680KA-A5 | CRYSTAL | 32.7680 kHz 12.5 pF | SMD | CRYSTAL 32.7680 kHz 12.5 pF SMD | X1 | 1 |  |  | EPSON | Digi-key | SER4103DKR-ND
92 | BATT CONTACT CLIP |  | PC PIN | BATT CONTACT CLIP PC PIN | BAT1,BAT2,BAT3,BAT4,BAT5,BAT6 | 12 | DNI |  | Keystone Elec | Digi-key | 36-92-ND
HV0810-2R7105-R | CAP | 1F -10% +30% 2.7V | RADIAL | CAP 1F -10% +30% 2.7V RADIAL | C11,C12 | 2 | DNI |  | Eaton | Digi-key | 283-4198-ND
G6SK-2 DC3 | RELAY TELECOM DPDT | 2A 250V | PC PIN | RELAY TELECOM DPDT 2A 250V PC PIN | RELAY1 | 1 | DNI |  | Omron | Digi-key | Z5234-ND
142-0701-871 | CONN SMA JACK STR | 50 OHM | BOARD EDGE | CONN SMA JACK STR 50 OHM BOARD EDGE | GNSS,IRIDIUM | 2 | DNI | Bulkhead Version, Enclosure Cutout: 7 mm diameter (1/4", 6.35 datasheet) | Cinch Connectivity | Digi-key | J610-ND
7101K2AV2QE | SWITCH TOGGLE SPDT | 5A 120V | PC PIN | SWITCH TOGGLE SPDT 5A 120V PC PIN | U53 | 1 | DNI | Enclosure Cutout: 7 mm diameter (1/4", 6.35 datasheet) | C&K | Digi-key | CKN1441-ND
1053091204 | CONN HEADER VERT MALE | 4POS 2.5MM | PIN | CONN HEADER VERT MALE 4POS 2.5MM PIN |  | 2 | DNI |  | Molex | Digi-key | WM14967-ND
1053071204 | NANOFIT RCPT |  |  | NANOFIT RCPT |  | 2 | DNI |  | Molex | Digi-key | WM14960-ND
1053002200 | NANOFIT CRIMP TERM |  |  | NANOFIT CRIMP TERM |  | 25 | DNI |  | Molex | Digi-key | WM14957CT-ND
LF10WBR-4S | CONN RCPT FMALE | 4POS |  | CONN RCPT FMALE 4POS |  | 2 | DNI | Enclosure cutout: 11.05 mm diameter datasheet (11 actual) | Hirose | Digi-key | HR557-ND
U.FL-2LP-088K1T-A-(50) | CBL ASSY U.FL PLUG-PLUG | 1.969" |  | CBL ASSY U.FL PLUG-PLUG 1.969" |  | 1 | DNI |  | Hirose | Digi-key | H125218-ND
95117A411 | PRESS-FIT NUT | 2-56 0.07" HEIGHT |  | PRESS-FIT NUT 2-56 0.07" HEIGHT | S1,S2 | 2 | DNI |  |  | McMaster-Carr | 95117A411
LCS_032_CTP | LIGHTPIPE THREADED |  |  | LIGHTPIPE THREADED |  | 1 | DNI | Enclosure cutout: 7.93 mm diameter datasheet (8 mm actual) | VCC | Digi-key | LCS_032_CTP-ND

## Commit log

2018-12-20 Adding extra batteries to board schematic and layout)
2019-01-02 preliminary changes to V5M board
2019-01-03 removing backup eagle files, edits to V5M PCB board
2019-01-03 Clean version of board modifications. Extra batteries, switch added. Reset button flipped to bottom. Moved USB port. NO EXTRA serial port yet.
2019-01-04 several changes to the board layout. Switched digital I/O lines for coil reset and charger shutdown. Added extra serial port.
2019-01-08 updated CAD file, BOM, Gerber files generated for initial version of the board
2019-01-15 Testing both serial ports in Arduino
2019-01-15 Board layout updated to pass OSH Park rules (mostly)
2019-01-17 Latest clean version of the board. Updated USB connector for 3 mil width polygons
2019-01-23 starting operational Iridium9603NBeacon_V5M arduiono code
2019-01-24 Working on operational code
2019-01-24 fixed some bugs
2019-02-04 Added diode to second battery pack
2019-02-15 Board as submitted to AAPCB
2019-02-21 updated BOM. started new operational code. Iridium9603NBeacon_V5M_XDATA
2019-02-21 working on XDATA operational code
2019-02-22 working on XDATA code
2019-03-01 working on debugging Iridium message
2019-03-13 repository at time of board shipment

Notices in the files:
parts and their libraries:
microbuilder: This work is placed in the public domain, and may be freely used for commercial and non-commercial work with the following conditions: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
SparkFun-Sensors: Licensing: CC v3.0 Share-Alike You are welcome to use this library for commercial purposes.
